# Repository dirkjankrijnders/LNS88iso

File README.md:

# LNS88iso
Isolated S88 loconet interface.

# BOM
|         Ref | Q. | Man.         | Man PN    | Farnell PN |
|-------------|----|--------------|-----------|------------|
|       IC101 | 1  | Atmel        | Attiny84- | 
|        U101 | 1  | Silicon Labs | Si8641b   | [2423287](http://nl.farnell.com/silicon-labs/si8641ab-b-is/digital-isolator-35ns-wsoic-16/dp/2423287 "Farnell")    |
|  U102, U103 | 2  | TI?          | 1117E50   |
|        U104 | 1  | ?            |           |

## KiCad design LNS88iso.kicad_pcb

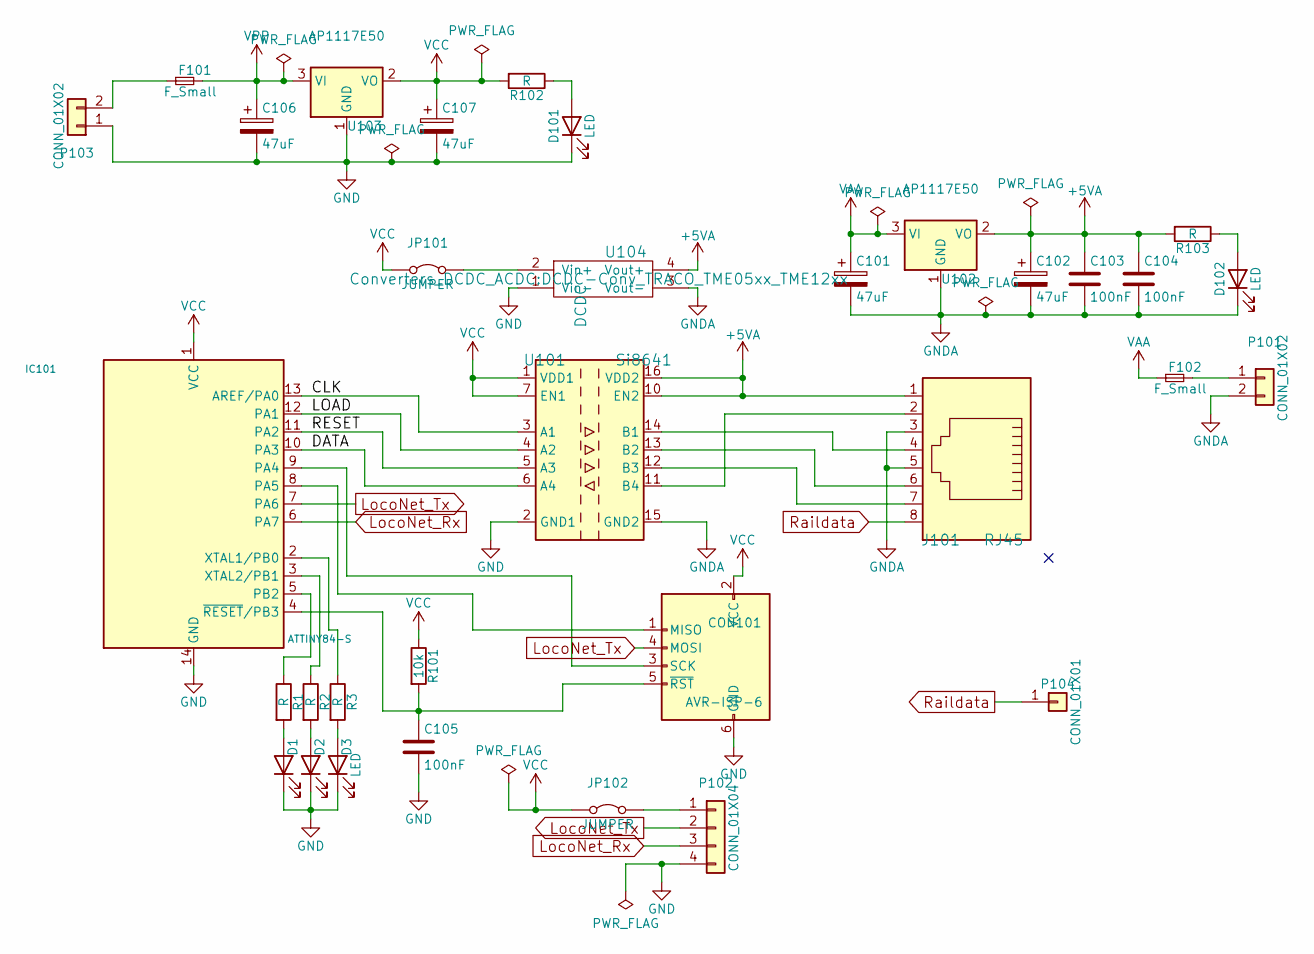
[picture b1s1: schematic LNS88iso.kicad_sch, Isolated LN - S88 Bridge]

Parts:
C101, C102, C106, C107: 47uF; c_elec_6.3x5.3
C103, C104, C105: 100nF; C_0805_HandSoldering
CON101: AVR-ISP-6; Pogopin_avr_isp
D1, D2, D3: LED; LED_0805_HandSoldering
D101, D102: LED; LED-0805
F101, F102: F_Small; Fuse_SMD1206_HandSoldering
IC101: ATTINY84-S; SOIC-14_3.9x8.7mm_P1.27mm
J101: RJ45; RJ45_8
JP101, JP102: JUMPER; Pin_Header_Straight_1x02
P101, P103: CONN_01X02; Pin_Header_Angled_1x02
P102: CONN_01X04; Pin_Header_Angled_1x04
P104: CONN_01X01; Pin_Header_Angled_1x01
R1, R2, R3, R102, R103: R; R_0805_HandSoldering
R101: 10k; R_0805_HandSoldering
U101: Si8641; SOIC-16_3.9x9.9mm_P1.27mm
U102, U103: AP1117E50; DPAK-3
U104: DCDC; DCDC-Conv_TRACO_TME05xx_TME12xx

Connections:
+5VA: C102.1, C103.1, C104.1, J101.1, R103.2, U101.10 (EN2), U101.16 (VDD2), U102.2 (VO), U104.4 (Vout+)
/CLK: IC101.13 (AREF/PA0), U101.3 (A1)
/DATA: IC101.10 (PA3), U101.6 (A4)
/LOAD: IC101.12 (PA1), U101.4 (A2)
/RESET: IC101.11 (PA2), U101.5 (A3)
GND: C105.2, C106.2, C107.2, CON101.6 (GND), D1.1 (K), D2.1 (K), D3.1 (K), D101.1 (K), IC101.14 (GND), P102.4, P103.1, U101.2 (GND1), U101.8 (GND1), U103.1 (GND), U104.1 (Vin-)
GNDA: C101.2, C102.2, C103.2, C104.2, D102.1 (K), J101.3, J101.5, P101.2, U101.9 (GND2), U101.15 (GND2), U102.1 (GND), U104.3 (Vout-)
LocoNet_Rx: IC101.6 (PA7), P102.3
LocoNet_Tx: CON101.4 (MOSI), IC101.7 (PA6), P102.2
unnamed: C105.1, CON101.5 (~RST), IC101.4 (~RESET/PB3), R101.2
unnamed: CON101.1 (MISO), IC101.8 (PA5)
unnamed: CON101.3 (SCK), IC101.9 (PA4)
unnamed: D1.2 (A), R1.2
unnamed: D2.2 (A), R2.2
unnamed: D3.2 (A), R3.2
unnamed: D101.2 (A), R102.1
unnamed: D102.2 (A), R103.1
unnamed: F101.1, P103.2
unnamed: F102.2, P101.1
unnamed: IC101.2 (XTAL1/PB0), R3.1
unnamed: IC101.3 (XTAL2/PB1), R2.1
unnamed: IC101.5 (PB2), R1.1
unnamed: J101.2, U101.11 (B4)
unnamed: J101.4, U101.14 (B1)
unnamed: J101.6, U101.13 (B2)
unnamed: J101.7, U101.12 (B3)
unnamed: JP101.2 (B), U104.2 (Vin+)
unnamed: JP102.2 (B), P102.1
Raildata: J101.8, P104.1
VAA: C101.1, F102.1, U102.3 (VI)
VCC: C107.1, CON101.2 (VCC), IC101.1 (VCC), JP101.1 (A), JP102.1 (A), R101.1, R102.2, U101.1 (VDD1), U101.7 (EN1), U103.2 (VO)
VPP: C106.1, F101.2, U103.3 (VI)

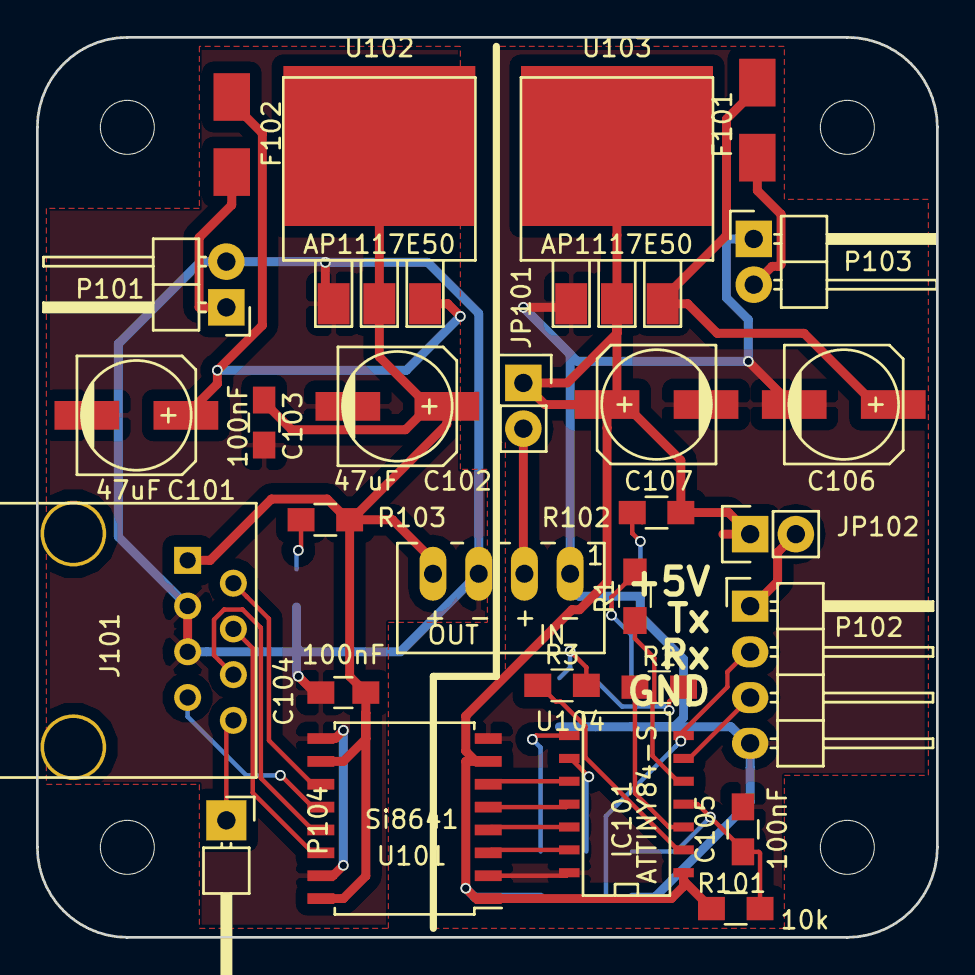
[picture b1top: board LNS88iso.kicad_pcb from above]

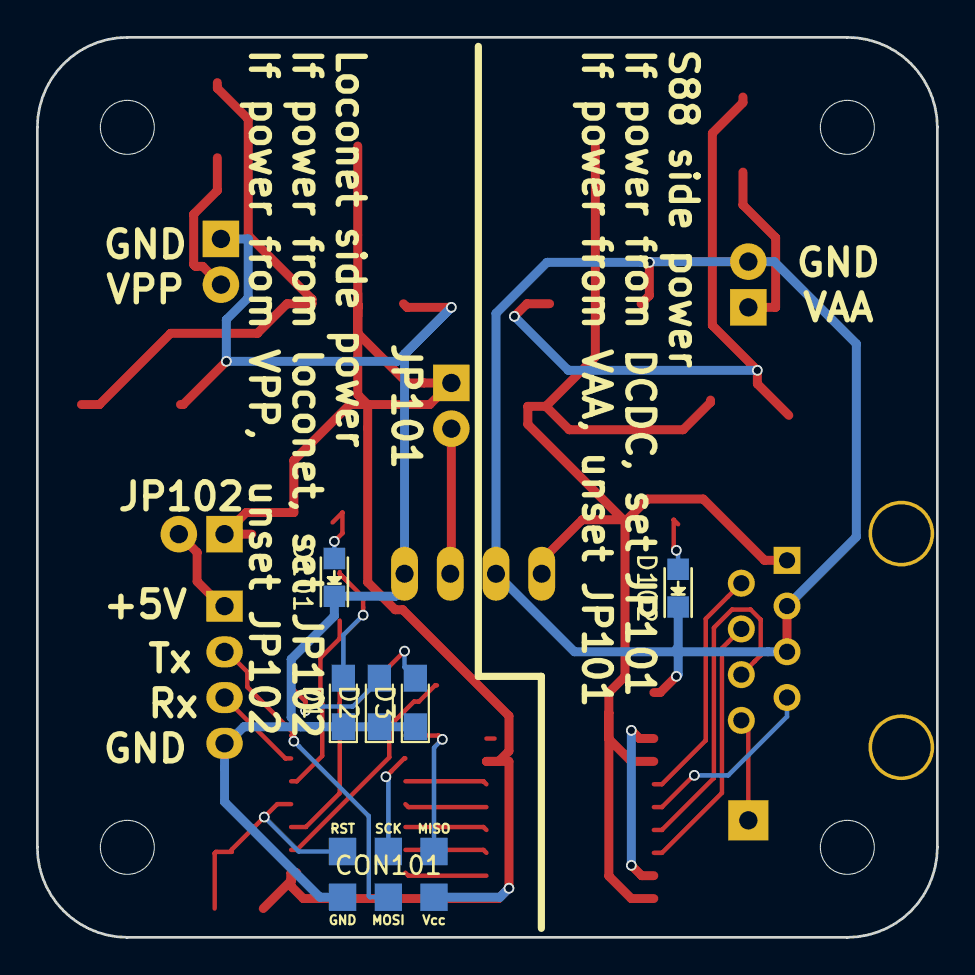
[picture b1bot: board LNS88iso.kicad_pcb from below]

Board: 2 copper layers, 50.0 x 50.0 mm, 33 parts (6 on the bottom side), 32 nets.

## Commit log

2015-09-15 Initial hardware
2015-09-15 Added pdf of schematic
2015-12-06 Lots of silkscreen fixes
2015-12-06 Start of full BOM
2015-12-06 Output files as send to board house
2016-02-10 First firmware code and platformio and travis configuration
2016-02-10 Removed the arduino code
2017-08-17 Fixed schematic symbolds
2017-08-18 Added labels to the wires
2017-08-18 Added LED's to the unused GPIO pins of the atttiny84, silkscreen may be improved at bit
2018-03-23 Indentation and S88 fixes, basic functionality works
2018-03-23 Fix? Loconet discovery
2019-10-21 Updated footprints to kicad 5.1 library
2025-03-14 Kicad updates
2025-03-14 Update to kicad 9
